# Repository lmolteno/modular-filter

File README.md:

Modular filters currently include:
 - All pass filter (phase shift as function of frequency, minimal amplitude response)
 - Low pass filter (10k-30k cutoff, i.e. distance filter, as higher frequencies get attenuated at distance)
 - Non-linear amplifier
 - Magnetic saturation with inductor (could fiddle with iron core as parameter)

The idea is to have a swappable bay of some description, with the right level of abstraction as it were that filter design becomes easy. For this reason, the connector has signal in, signal out, +5V, -5V and ground.
Ideally, aesthetics will also not be horrible.

# V1
V1's construction was alright, though there were mistakes made on the values of capacitor bought, so performance was mediocre.
The input stage had some issues, solved by swapping the T and R on the input to the opamp (i.e. inverting the inputs).
The bypass also causes strange issues where it over the course of a few seconds causes greater and greater amounts of clipping on the input signal.

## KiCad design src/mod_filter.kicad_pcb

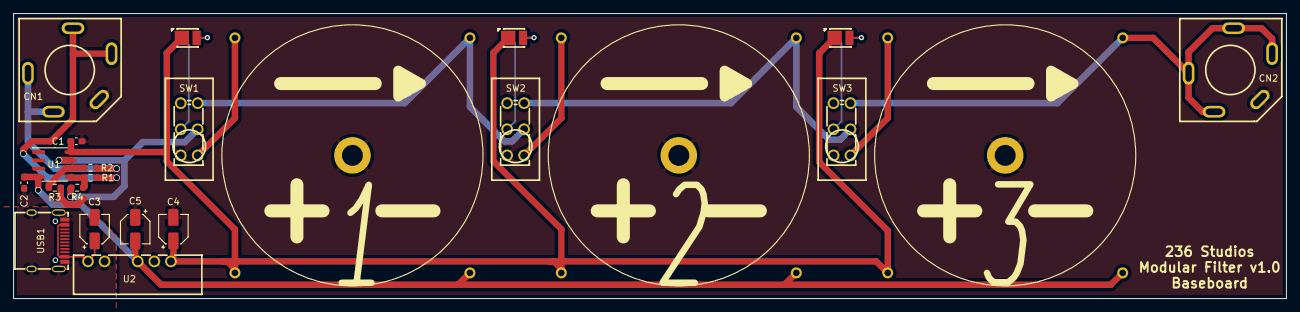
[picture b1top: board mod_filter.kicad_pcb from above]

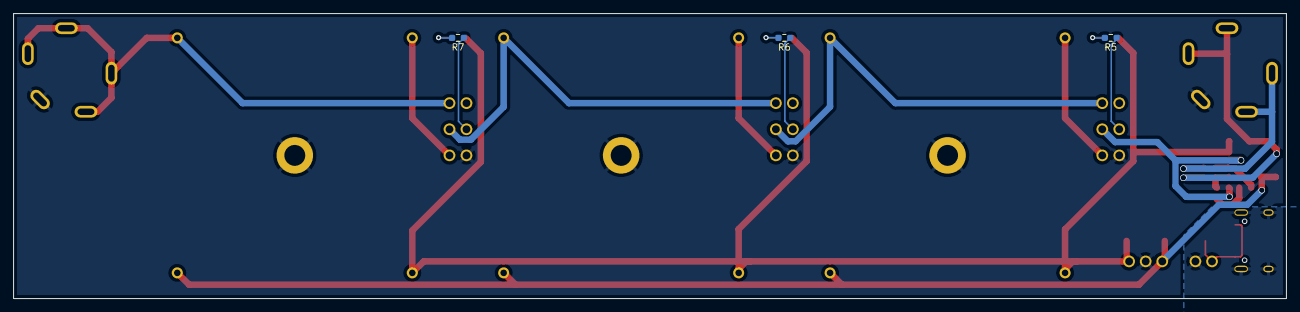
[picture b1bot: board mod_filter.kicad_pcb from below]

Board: 2 copper layers, 195.0 x 43.7 mm, 26 parts (3 on the bottom side), 22 nets.

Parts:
C1, C2: 0.1u; C_0603_1608Metric_Pad1.08x0.95mm_HandSolder
C3, C4, C5: 4.7u; CP_Elec_4x5.4
CN1: INPUT; AUDIO-TH_CK6.35-3-14-18LF
CN2: OUTPUT; AUDIO-TH_CK6.35-3-14-18LF
F1, F2, F3: Molteno_Filter
LED1, LED2, LED3: RED; LED-SMD_L3.5-W2.8-R-FD_TJ-S2835UG5W8TLC2R-A5
R1, R2, R3, R4: 1K; R_0603_1608Metric_Pad0.98x0.95mm_HandSolder
R5, R6, R7: 220; R_0603_1608Metric_Pad0.98x0.95mm_HandSolder
SW1, SW2, SW3: BYPASS; SW-TH_SS-22F24AT10
U1: TL062; SOIC-8_3.9x4.9mm_P1.27mm
U2: A0505S-1WR3; PWRM-TH_A05XXS-1WR3
USB1: TYPEC-304-BCP16; USB-C-SMD_TYPEC-304-BCP16

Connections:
5V_GND: C3.2, U2.2 (GND), USB1.13 (GND), USB1.14 (GND), USB1.15 (GND), USB1.16 (GND), USB1.A1B12 (GND), USB1.B1A12 (GND)
5V_IN: C3.1, U2.1 (VIN), USB1.A4B9 (VBUS), USB1.B4A9 (VBUS)
+5V: C1.1, C4.1, F1.3 (V+), F2.3 (V+), F3.3 (V+), LED1.2 (+), LED2.2 (+), LED3.2 (+), U1.8 (V+), U2.6 (+VO)
-5V: C2.1, C5.2, F1.4 (V-), F2.4 (V-), F3.4 (V-), U1.4 (V-), U2.4 (-VO)
/1->2: F1.2 (OUT), SW1.6, SW2.5
/2->3: F2.2 (OUT), SW2.6, SW3.5
/IN_R: CN1.2, CN1.4, R2.1
/IN_T: CN1.3, CN1.5, R1.1
GND: C1.2, C2.2, C4.2, C5.1, CN1.1, CN2.1, F1.5 (GND), F2.5 (GND), F3.5 (GND), R3.1, SW1.1, SW2.1, SW3.1, U2.5 (0V)
IN: R4.2, SW1.5, U1.7
unnamed: F1.1 (IN), SW1.4
unnamed: F2.1 (IN), SW2.4
unnamed: F3.1 (IN), SW3.4
unnamed: LED1.1 (-), R5.2
unnamed: LED2.1 (-), R6.2
unnamed: LED3.1 (-), R7.2
unnamed: R1.2, R4.1, U1.5 (+)
unnamed: R2.2, R3.2, U1.6 (-)
unnamed: R5.1, SW1.2
unnamed: R6.1, SW2.2
unnamed: R7.1, SW3.2
TS_OUT: CN2.2, CN2.3, CN2.4, CN2.5, F3.2 (OUT), SW3.6

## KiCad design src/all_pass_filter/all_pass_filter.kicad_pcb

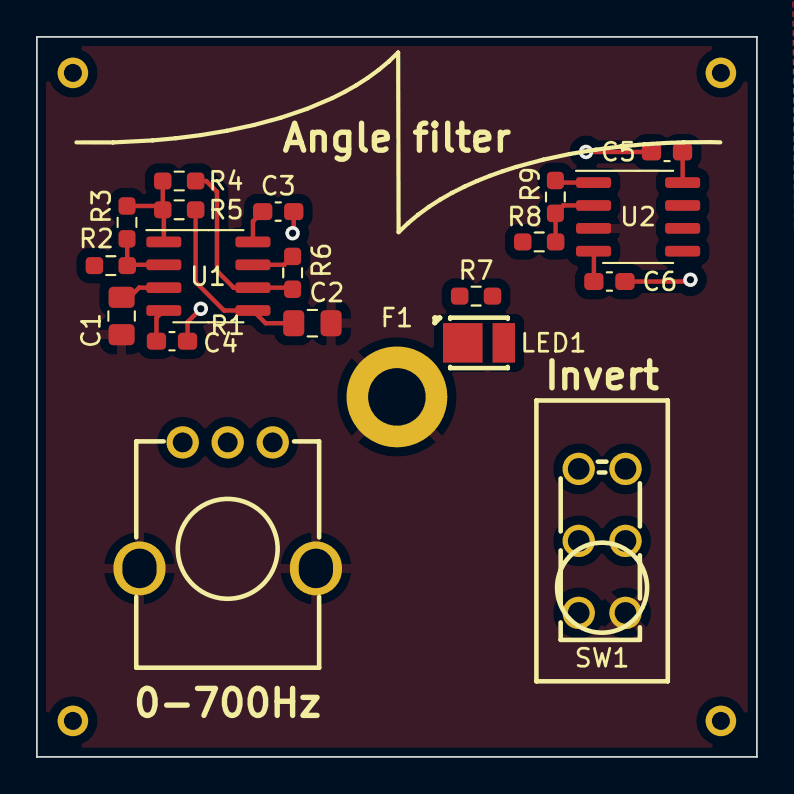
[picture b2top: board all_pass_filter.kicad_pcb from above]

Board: 4 copper layers, 40.0 x 40.0 mm, 20 parts (0 on the bottom side), 19 nets.

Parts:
C1, C2: 4.7u; C_0805_2012Metric_Pad1.18x1.45mm_HandSolder
C3, C4, C5, C6: 0.1u; C_0603_1608Metric_Pad1.08x0.95mm_HandSolder
F1: Molteno_Filter; Molteno_Filter_Clean
LED1: INVERT_INDICATOR; LED-SMD_L3.5-W2.8-R-FD_TJ-S2835UG5W8TLC2R-A5
R1: 5k; RES-ADJ-TH_RK09K1130AJ3
R2, R3, R4, R6, R8, R9: 100; R_0603_1608Metric_Pad0.98x0.95mm_HandSolder
R5: 2.2k; R_0603_1608Metric_Pad0.98x0.95mm_HandSolder
R7: 220; R_0603_1608Metric_Pad0.98x0.95mm_HandSolder
SW1: INVERT; SW-TH_SS-22F24AT10
U1, U2: LM833; SOIC-8_3.9x4.9mm_P1.27mm

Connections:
+5V: C3.2, C5.2, F1.3 (V+)
-5V: C4.2, C6.2, F1.4 (V-)
AP_OUT: R6.2, SW1.2, U1.7
GND: C1.2, C2.2, F1.5 (GND), R1.4, R1.5, SW1.4, U2.3 (+)
IN: F1.1 (IN), R1.2, R2.1
INV_IN: R8.1, SW1.1
unnamed: C1.1, R1.3, U1.3 (+)
unnamed: C2.1, R5.2, U1.5 (+)
unnamed: LED1.1 (-), R7.2
unnamed: R2.2, R3.1, U1.2 (-)
unnamed: R3.2, R4.1, R5.1, U1.1
unnamed: R4.2, R6.1, U1.6 (-)
unnamed: R7.1, SW1.5
unnamed: R8.2, R9.1, U2.2 (-)
unnamed: C4.1, U1.4 (V-)
unnamed: C3.1, U1.8 (V+)
unnamed: C6.1, U2.4 (V-)
unnamed: C5.1, U2.8 (V+)
OUT: F1.2 (OUT), R9.2, SW1.3, U2.1
